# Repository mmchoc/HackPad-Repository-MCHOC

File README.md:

# SideDuck Macropad 

SideDuck is a 9 key macropad that utilizes KMK firmware and a keyboard matrix circuit. This macropad includes 2 SK6812 MINI-E LEDs as well as customizable LED features including a reactive ripple effect. 

It serves as an extension to my 60% keyboard providing my setup with individual arrow keys as well as a delete key 

## Features 

- 2 SK6812 MINI-E LEDs
- Breathe and Reactive LED feature
- Home Key as the Layer-Tap Key 
- 9 Keys

## CAD Model 

2-Piece case that fits together utilizing 4 M3 Bolts and heatset inserts. 

The case model was made in Fusion360 

## PCB 
This is my PCB that utilizes a matrix circuit to reduce the amount of ports tied to each switch. Every switch organized in rows and columns with their respective diodes and connected to the XIAO RP2040 respectively. 

This is my Schematic 

This is my PCB 

## Firmware Overview 
This macropad uses KMK firmware for everything 
- The home key acts as a Layer-Tap Key
- LED choices of Off, Reactive, and Breathe mode

## BOM:

- 9x Cherry MX Switches
- 9x Blank DSA Keycaps
- 4x M3x5x4 Heatset inserts
- 4x M3x16mm SHCS Bolts
- 9x 1N4148 DO-35 Diodes
- 2x SK6812 MINI-E LEDs
- 1x XIAO RP2040
- 1x Case (Two 3D printed parts)

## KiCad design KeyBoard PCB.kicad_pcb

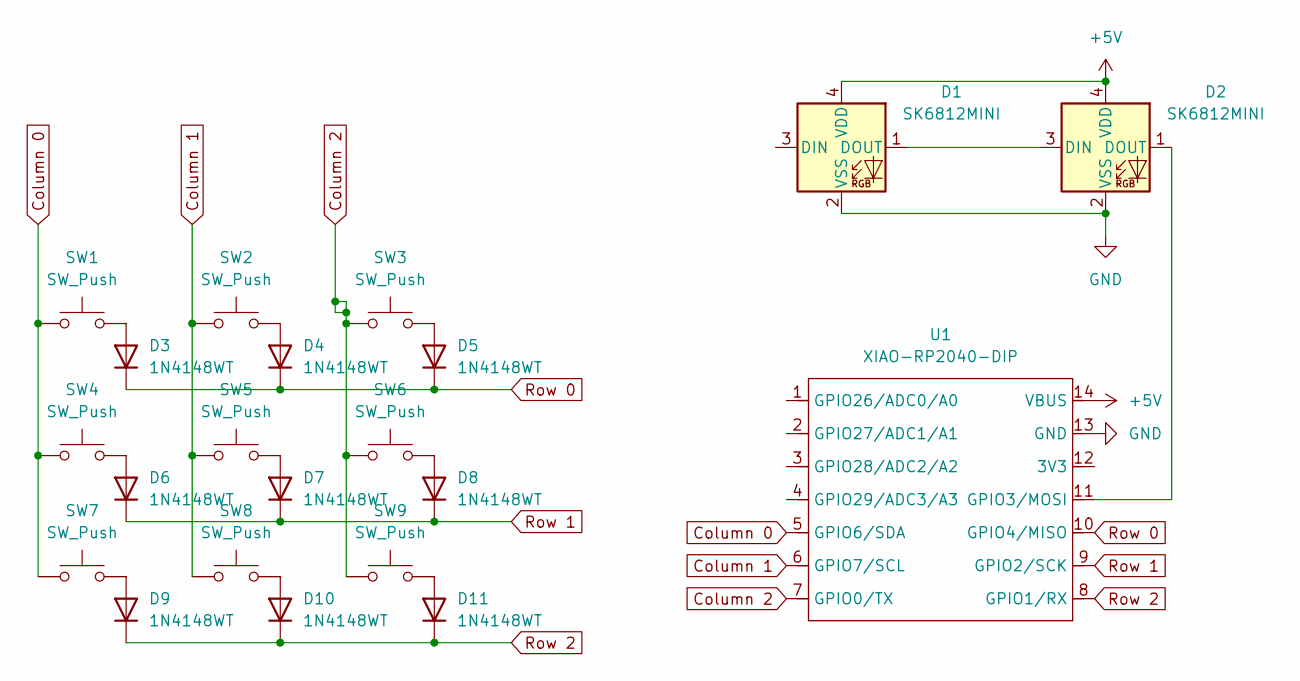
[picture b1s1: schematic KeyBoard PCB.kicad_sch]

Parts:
D1, D2: SK6812MINI; LED_SK6812MINI_PLCC4_3.5x3.5mm_P1.75mm
D3, D4, D5, D6, D7, D8, D9, D10, D11: 1N4148WT; D_DO-35_SOD27_P7.62mm_Horizontal
SW1, SW2, SW3, SW4, SW5, SW6, SW7, SW8, SW9: SW_Push; SW_Cherry_MX_1.00u_PCB
U1: XIAO-RP2040-DIP

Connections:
+5V: D1.4 (VDD), D2.4 (VDD), U1.14 (VBUS)
Column 0: SW1.1, SW4.1, SW7.1, U1.5 (GPIO6/SDA)
Column 1: SW2.1, SW5.1, SW8.1, U1.6 (GPIO7/SCL)
Column 2: SW3.1, SW6.1, SW9.1, U1.7 (GPIO0/TX)
GND: D1.2 (VSS), D2.2 (VSS), U1.13 (GND)
unnamed: D1.1 (DOUT), D2.3 (DIN)
unnamed: D2.1 (DOUT), U1.11 (GPIO3/MOSI)
unnamed: D3.2 (A), SW1.2
unnamed: D4.2 (A), SW2.2
unnamed: D5.2 (A), SW3.2
unnamed: D6.2 (A), SW4.2
unnamed: D7.2 (A), SW5.2
unnamed: D8.2 (A), SW6.2
unnamed: D9.2 (A), SW7.2
unnamed: D10.2 (A), SW8.2
unnamed: D11.2 (A), SW9.2
Row 0: D3.1 (K), D4.1 (K), D5.1 (K), U1.10 (GPIO4/MISO)
Row 1: D6.1 (K), D7.1 (K), D8.1 (K), U1.9 (GPIO2/SCK)
Row 2: D9.1 (K), D10.1 (K), D11.1 (K), U1.8 (GPIO1/RX)

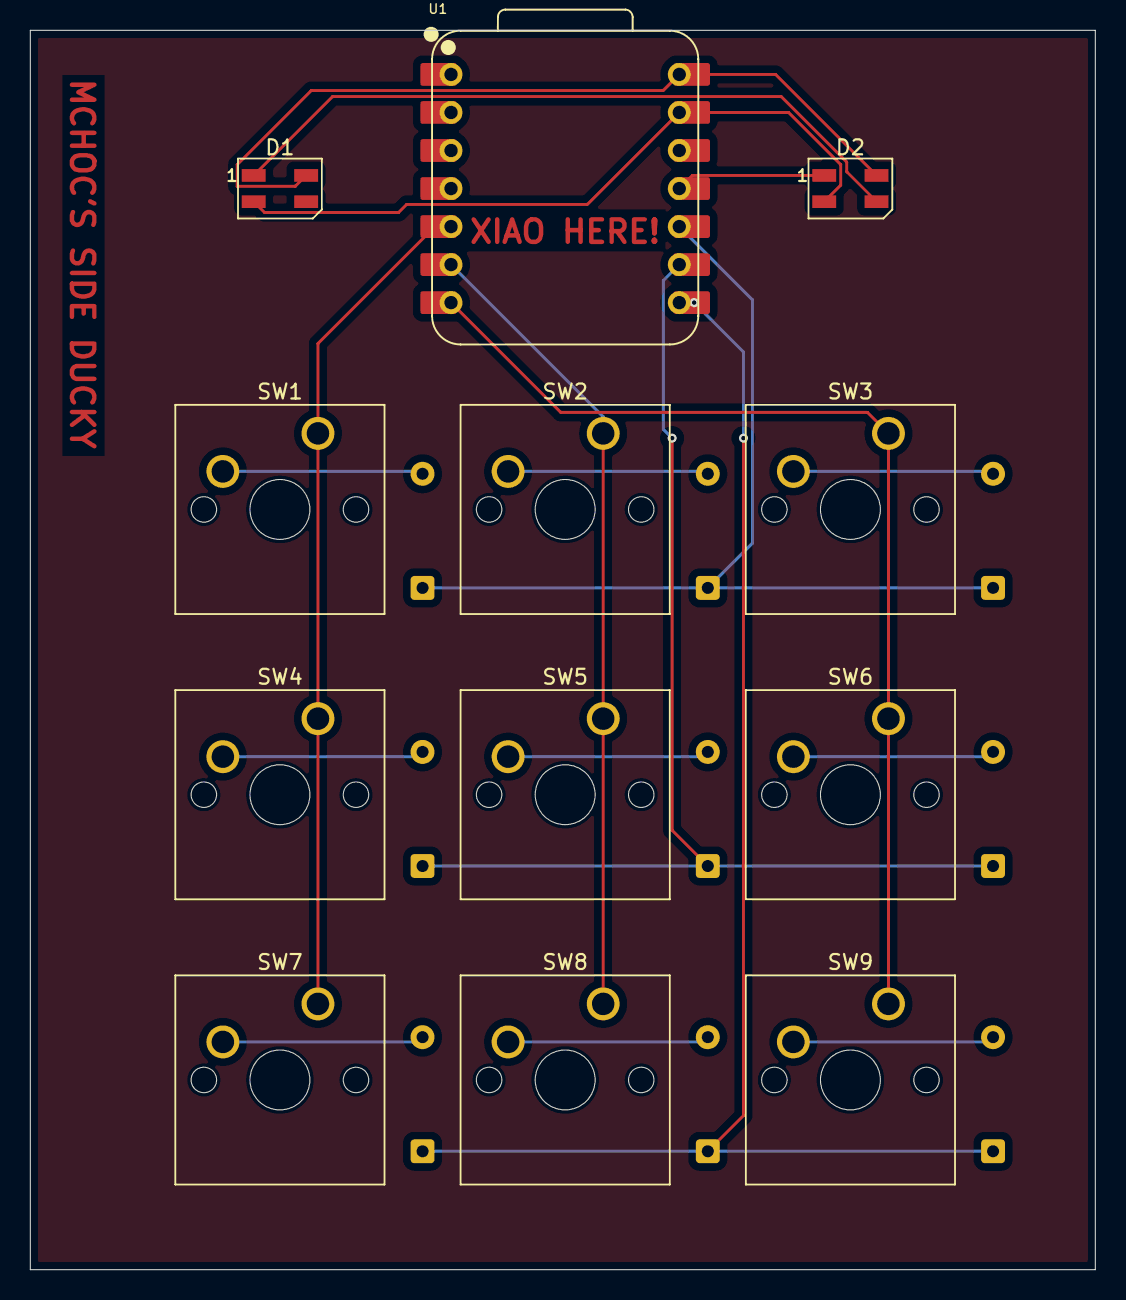
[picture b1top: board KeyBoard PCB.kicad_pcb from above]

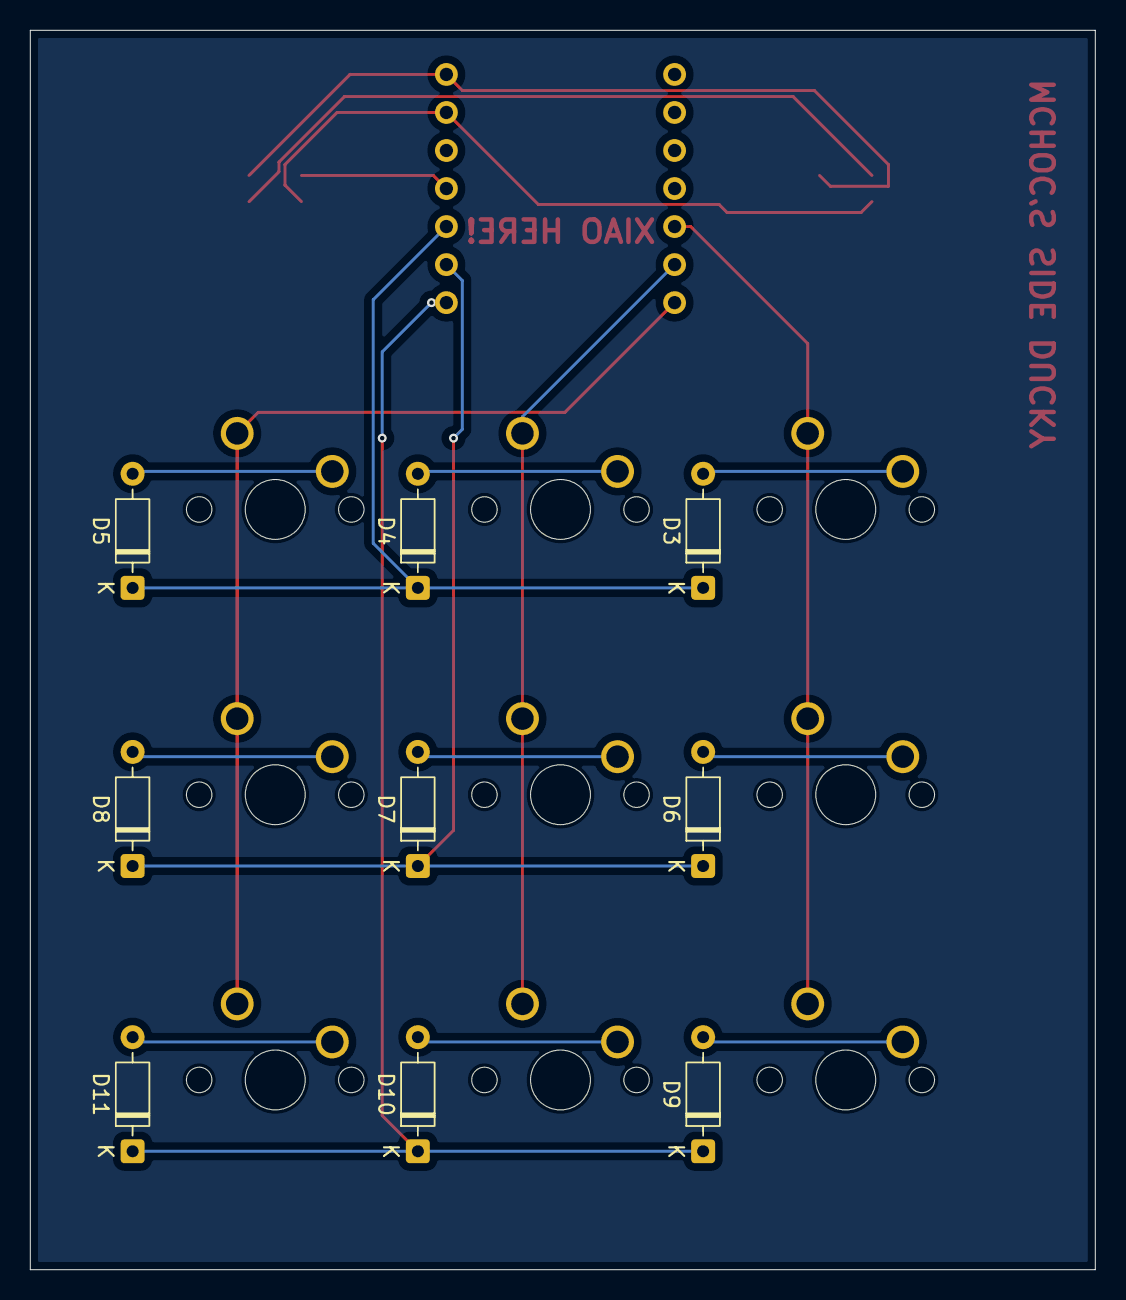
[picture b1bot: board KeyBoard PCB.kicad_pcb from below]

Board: 2 copper layers, 71.1 x 82.8 mm, 21 parts (9 on the bottom side), 19 nets.

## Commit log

2025-12-20 README.md
